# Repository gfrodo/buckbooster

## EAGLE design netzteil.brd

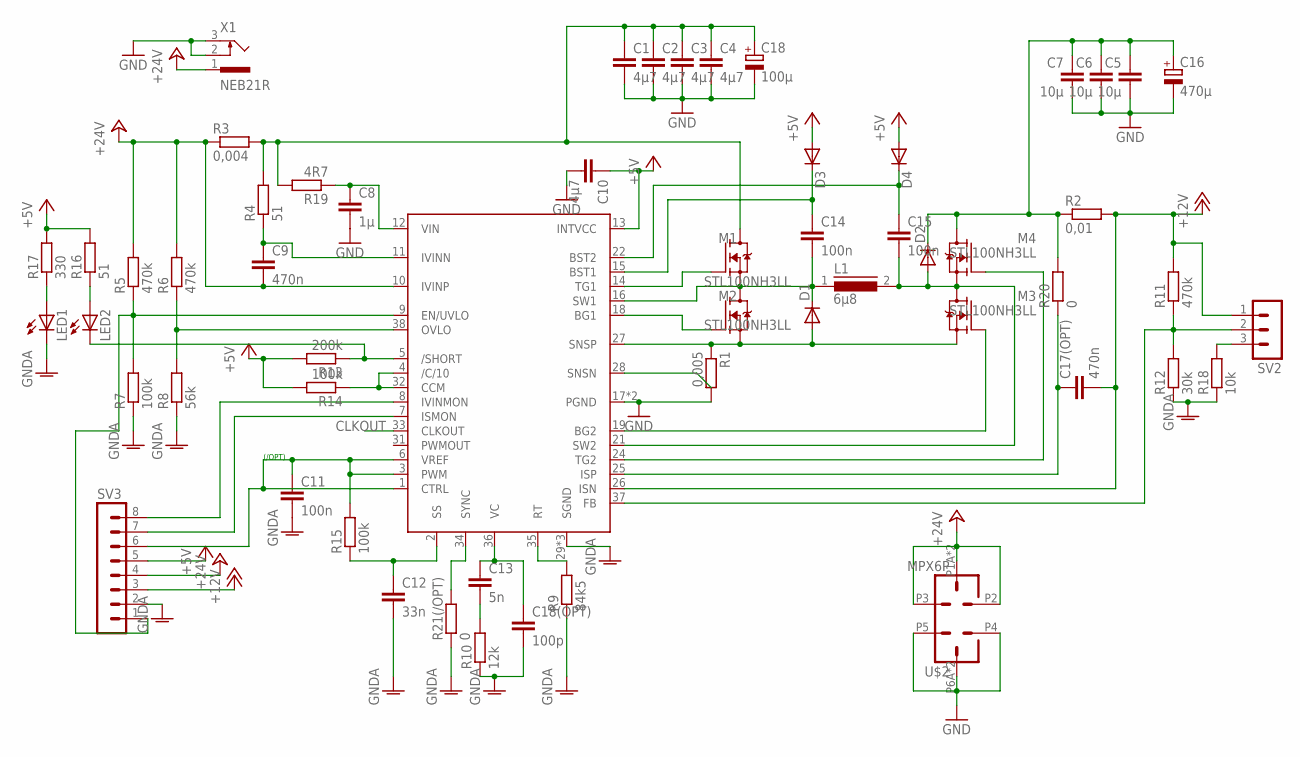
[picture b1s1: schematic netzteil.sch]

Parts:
C1, C2, C3, C4: 4µ7; C1206K
C5, C6, C7: 10µ; C1206K
C8: 1µ; C0805K
C9, C17(OPT): 470n; C0805K
C10: 4µ7; C0805K
C11, C14, C15: 100n; C0805K
C12: 33n; C0805K
C13: 5n; C0805K
C16: 470µ; 153CLV-1010
C18: 100µ; 153CLV-0605
C18(OPT): 100p; C0805K
D1, D2, D3, D4: DIODE-SOD323-R; SOD323-R
L1: 6µ8; DR125
LED1, LED2: LEDSML0805; SML0805
M1, M2, M3, M4: STL100NH3LL; PG-TDSON-8
R1: 0,005; R2512
R2: 0,01; R2512
R3: 0,004; R2512
R4, R16: 51; M0805
R5, R6, R11: 470k; M0805
R7, R14, R15: 100k; M0805
R8: 56k; M0805
R9: 84k5; M0805
R10: 12k; M0805
R12: 30k; M0805
R13: 200k; M0805
R17: 330; M0805
R18: 10k; M0805
R19: 4R7; M0805
R20, R21(/OPT): 0; M0805
SV2: MA03-1
SV3: MA08-1
U$1: LT3790; HTSSOP38DCP
U$2: MPX6P; MPX6
X1: NEB21R

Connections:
+5V: C10.1, D3.A, D4.A, R13.2, R14.2, R16.2, R17.2, SV3.5, U$1.13 (INTVCC)
+12V: C17(OPT).2, R2.2, R11.2, SV2.1, SV3.3, U$1.26 (ISN)
+24V: C9.2, R3.1, R5.2, R6.2, SV3.4, U$1.10 (IVINP), U$2.P1A (1), U$2.P1B (1), U$2.P2 (2), U$2.P3 (3), X1.1
BG1: M2.4 (G), U$1.18 (BG1)
BG2: M3.4 (G), U$1.19 (BG2)
BST1: C14.1, D3.C, U$1.15 (BST1)
BST2: C15.1, D4.C, U$1.22 (BST2)
CLKOUT: U$1.33 (CLKOUT)
GND: C1.2, C2.2, C3.2, C4.2, C5.2, C6.2, C7.2, C8.2, C10.2, C16.-, C18.-, R1.2, U$1.17 (PGND), U$1.20 (PGND), U$2.P4 (4), U$2.P5 (5), U$2.P6A (6), U$2.P6B (6), X1.2, X1.3
GNDA: C11.2, C12.2, C18(OPT).2, LED1.C, R7.1, R8.1, R9.1, R10.1, R12.1, R18.1, R21(/OPT).1, SV3.2, U$1.29 (SGND), U$1.30 (SGND), U$1.EXP@1 (SGND)
ISP: C5.1, C6.1, C7.1, C16.+, D2.C, M4.5 (D), M4.6 (D), M4.7 (D), M4.8 (D), M4.TH (D), R2.1, R20.2
unnamed: SV3.7, U$1.7 (ISMON)
unnamed: SV3.8, U$1.8 (IVINMON)
unnamed: LED1.A, R17.1
unnamed: LED2.A, R16.1
unnamed: R18.2, SV2.3
unnamed: C13.2, R10.2
unnamed: C13.1, C18(OPT).1, U$1.36 (VC)
unnamed: C8.1, R19.1, U$1.12 (VIN)
unnamed: C17(OPT).1, R20.1, U$1.25 (ISP)
unnamed: C9.1, R4.1, U$1.11 (IVINN)
unnamed: R5.1, R7.2, SV3.1, U$1.9 (EN/UVLO)
unnamed: R6.1, R8.2, U$1.38 (OVLO)
unnamed: R11.1, R12.2, SV2.2, U$1.37 (FB)
unnamed: R14.1, U$1.4 (/C/10), U$1.32 (CCM)
unnamed: LED2.C, R13.1, U$1.5 (/SHORT)
unnamed: C12.1, R15.1, U$1.2 (SS)
unnamed: R9.2, U$1.35 (RT)
unnamed: C11.1, R15.2, SV3.6, U$1.1 (CTRL), U$1.3 (PWM), U$1.6 (VREF)
SNSP: D1.A, M2.1 (S), M2.2 (S), M2.3 (S), M3.1 (S), M3.2 (S), M3.3 (S), R1.1, U$1.27 (SNSP)
SW1: C14.2, D1.C, L1.1, M1.1 (S), M1.2 (S), M1.3 (S), M2.5 (D), M2.6 (D), M2.7 (D), M2.8 (D), M2.TH (D), U$1.16 (SW1)
SW2: C15.2, D2.A, L1.2, M3.5 (D), M3.6 (D), M3.7 (D), M3.8 (D), M3.TH (D), M4.1 (S), M4.2 (S), M4.3 (S), U$1.21 (SW2)
SYNC: R21(/OPT).2, U$1.34 (SYNC)
TG1: M1.4 (G), U$1.14 (TG1)
TG2: M4.4 (G), U$1.24 (TG2)
VINN: C1.1, C2.1, C3.1, C4.1, C18.+, M1.5 (D), M1.6 (D), M1.7 (D), M1.8 (D), M1.TH (D), R3.2, R4.2, R19.2

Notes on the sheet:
(/OPT)

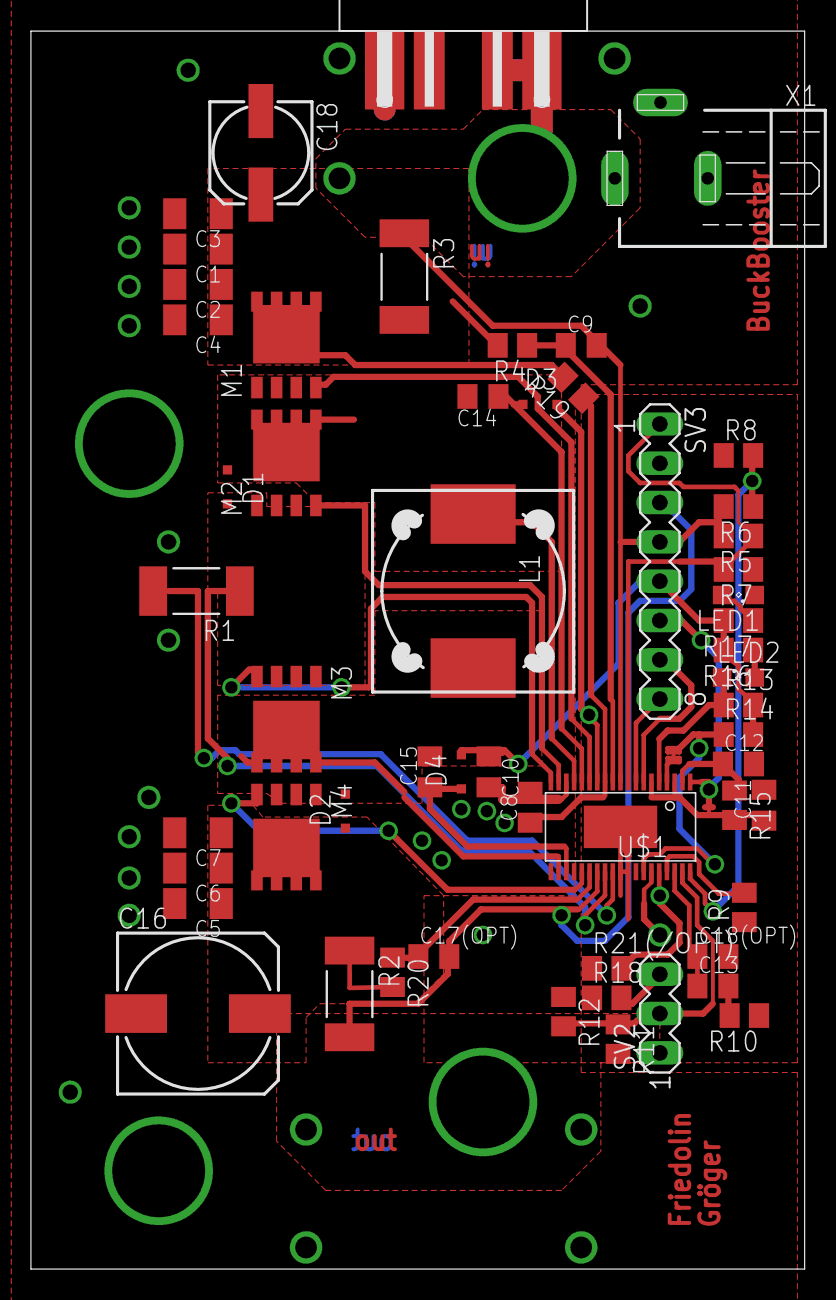
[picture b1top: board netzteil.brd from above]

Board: 2 copper layers, 50.0 x 80.0 mm, 56 parts (0 on the bottom side), 35 nets.

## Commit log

2016-01-28 initial
2016-01-28 version1
2016-01-28 version2
2016-01-28 version3
2016-01-28 an platinenbelichter gesendet, hohlstecker verpolt
2016-01-28 platine V1 gefertigt
2016-01-28 version v1 bestückt
2016-01-28 version 2
2016-02-10 akkustecker
2016-02-12 polygon corrections, document layer for circles
2016-02-12 enable/undervoltage on pin header
2016-03-25 gitignore updated
